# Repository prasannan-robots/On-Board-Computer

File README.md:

## Low Cost Onboard pcb for cubesat
Features:
- Redundant Control
- i2c external communication
- Power via 5v 3.3v
- Inbuilt temperature Monitoring

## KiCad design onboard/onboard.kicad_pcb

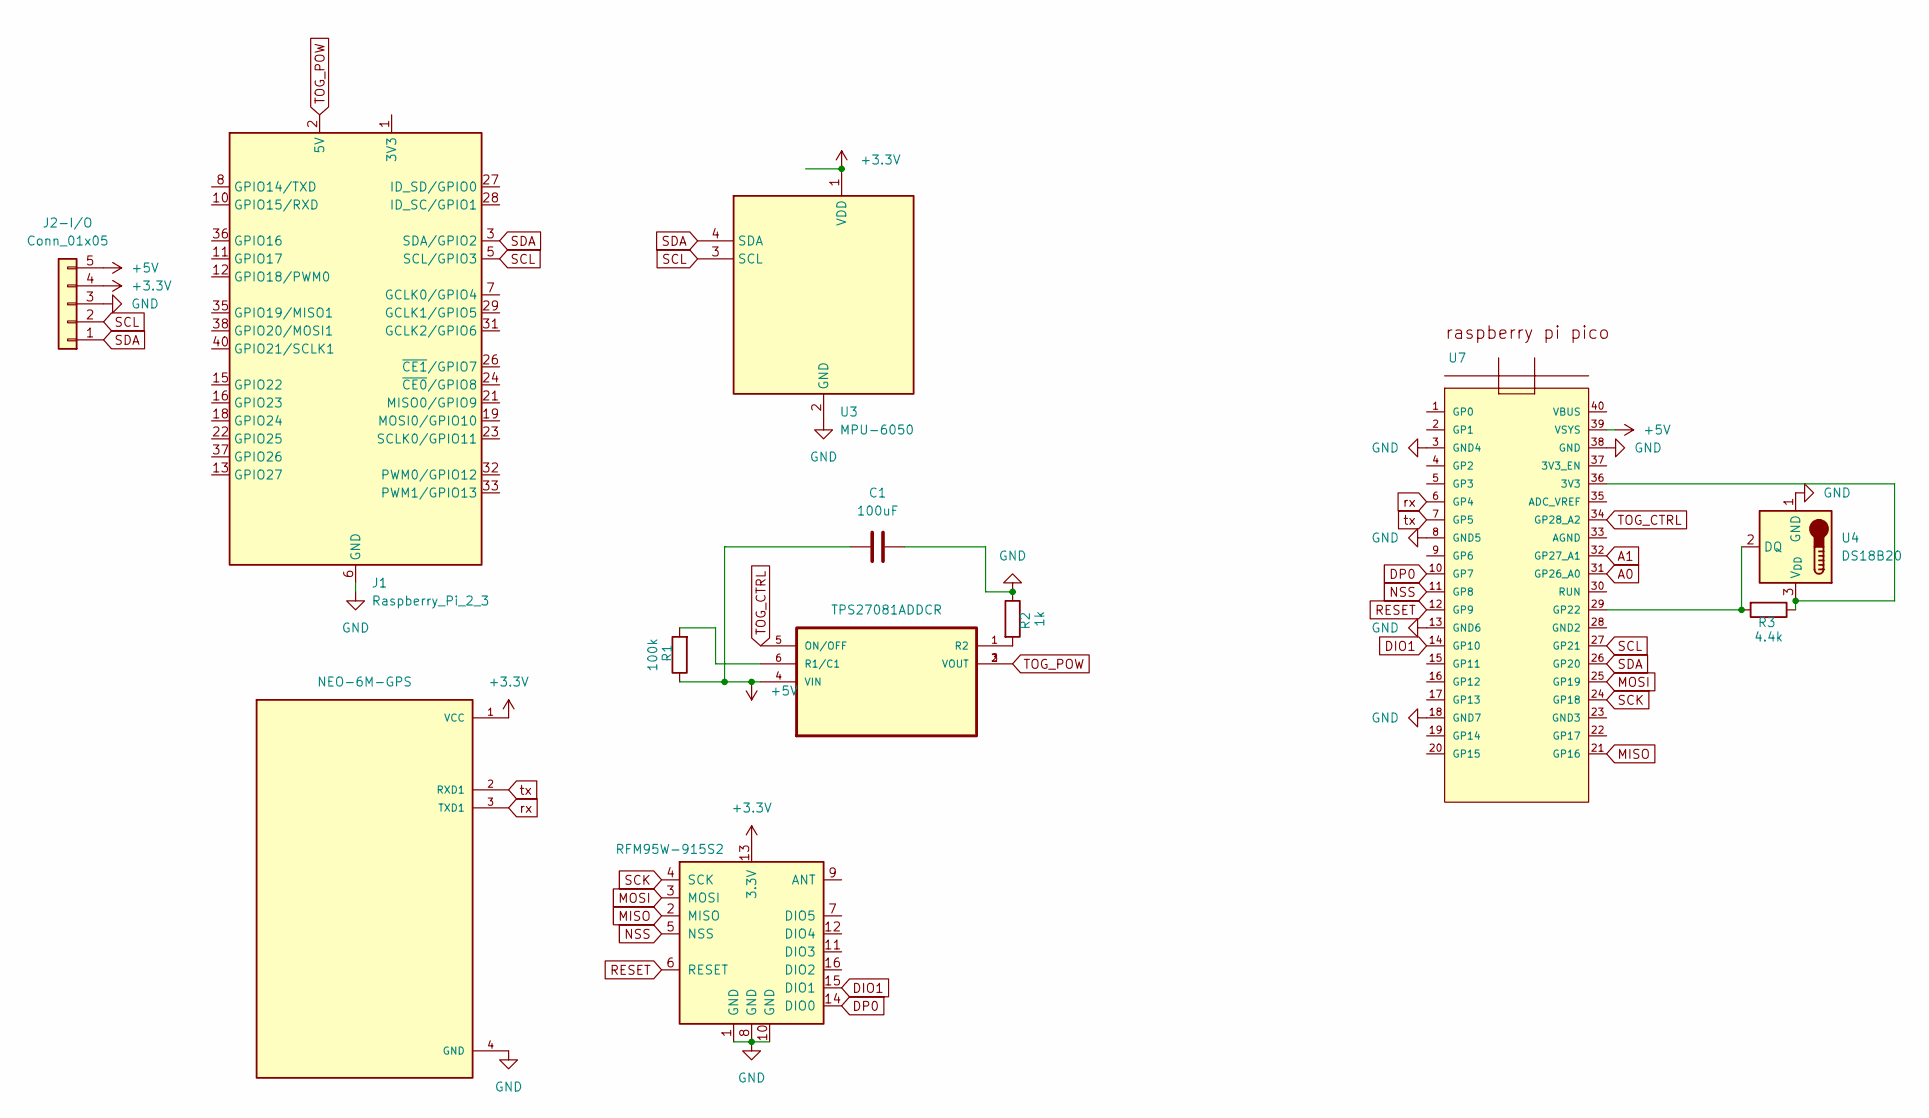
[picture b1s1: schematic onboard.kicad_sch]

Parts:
C1: 100uF; CP_Radial_D6.3mm_P2.50mm
J1: Raspberry_Pi_2_3; PinSocket_2x20_P2.54mm_Vertical
J2-I/O: Conn_01x05; PinSocket_1x05_P2.54mm_Vertical
R1: 100k; R_Axial_DIN0204_L3.6mm_D1.6mm_P7.62mm_Horizontal
R2: 1k; R_Axial_DIN0204_L3.6mm_D1.6mm_P7.62mm_Horizontal
R3: 4.4k; R_Axial_DIN0204_L3.6mm_D1.6mm_P7.62mm_Horizontal
U1: RFM95W-915S2; HOPERF_RFM9XW_THT
U2: NEO-6M-GPS; PinSocket_1x04_P2.54mm_Vertical; PARTREV R15
U3: MPU-6050; PinSocket_1x08_P2.54mm_Vertical
U4: DS18B20; TO-92_Inline
U5: TPS27081ADDCR; SOT95P280X110-6N
U7: RASPBERRY_PI_PICO; RaspberryPi_Pico_Common_THT

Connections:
+3.3V: J2-I/O.4, U1.13 (3.3V), U2.1 (VCC), U3.1 (VDD)
+5V: C1.1, J2-I/O.5, R1.1, U5.4 (VIN), U7.39 (VSYS)
A0: U7.31 (GP26_A0)
A1: U7.32 (GP27_A1)
DIO1: U1.15 (DIO1), U7.14 (GP10)
DP0: U1.14 (DIO0), U7.10 (GP7)
GND: C1.2, J1.6 (GND), J1.9 (GND), J1.14 (GND), J1.20 (GND), J1.25 (GND), J1.30 (GND), J1.34 (GND), J1.39 (GND), J2-I/O.3, R2.1, U1.1 (GND), U1.8 (GND), U1.10 (GND), U2.4 (GND), U3.2 (GND), U4.1 (GND), U7.3 (GND4), U7.8 (GND5), U7.13 (GND6), U7.18 (GND7), U7.38 (GND)
MISO: U1.2 (MISO), U7.21 (GP16)
MOSI: U1.3 (MOSI), U7.25 (GP19)
NSS: U1.5 (NSS), U7.11 (GP8)
unnamed: J1.1 (3V3), J1.17 (3V3)
unnamed: R3.2, U4.2 (DQ), U7.29 (GP22)
unnamed: R3.1, U4.3 (V_{DD}), U7.36 (3V3)
unnamed: R1.2, U5.6 (R1/C1)
unnamed: R2.2, U5.1 (R2)
RESET: U1.6 (RESET), U7.12 (GP9)
SCK: U1.4 (SCK), U7.24 (GP18)
SCL: J1.5 (SCL/GPIO3), J2-I/O.2, U3.3 (SCL), U7.27 (GP21)
SDA: J1.3 (SDA/GPIO2), J2-I/O.1, U3.4 (SDA), U7.26 (GP20)
TOG_CTRL: U5.5 (ON/OFF), U7.34 (GP28_A2)
TOG_POW: J1.2 (5V), J1.4 (5V), U5.2 (VOUT), U5.3 (VOUT)
rx: U2.3 (TXD1), U7.6 (GP4)
tx: U2.2 (RXD1), U7.7 (GP5)

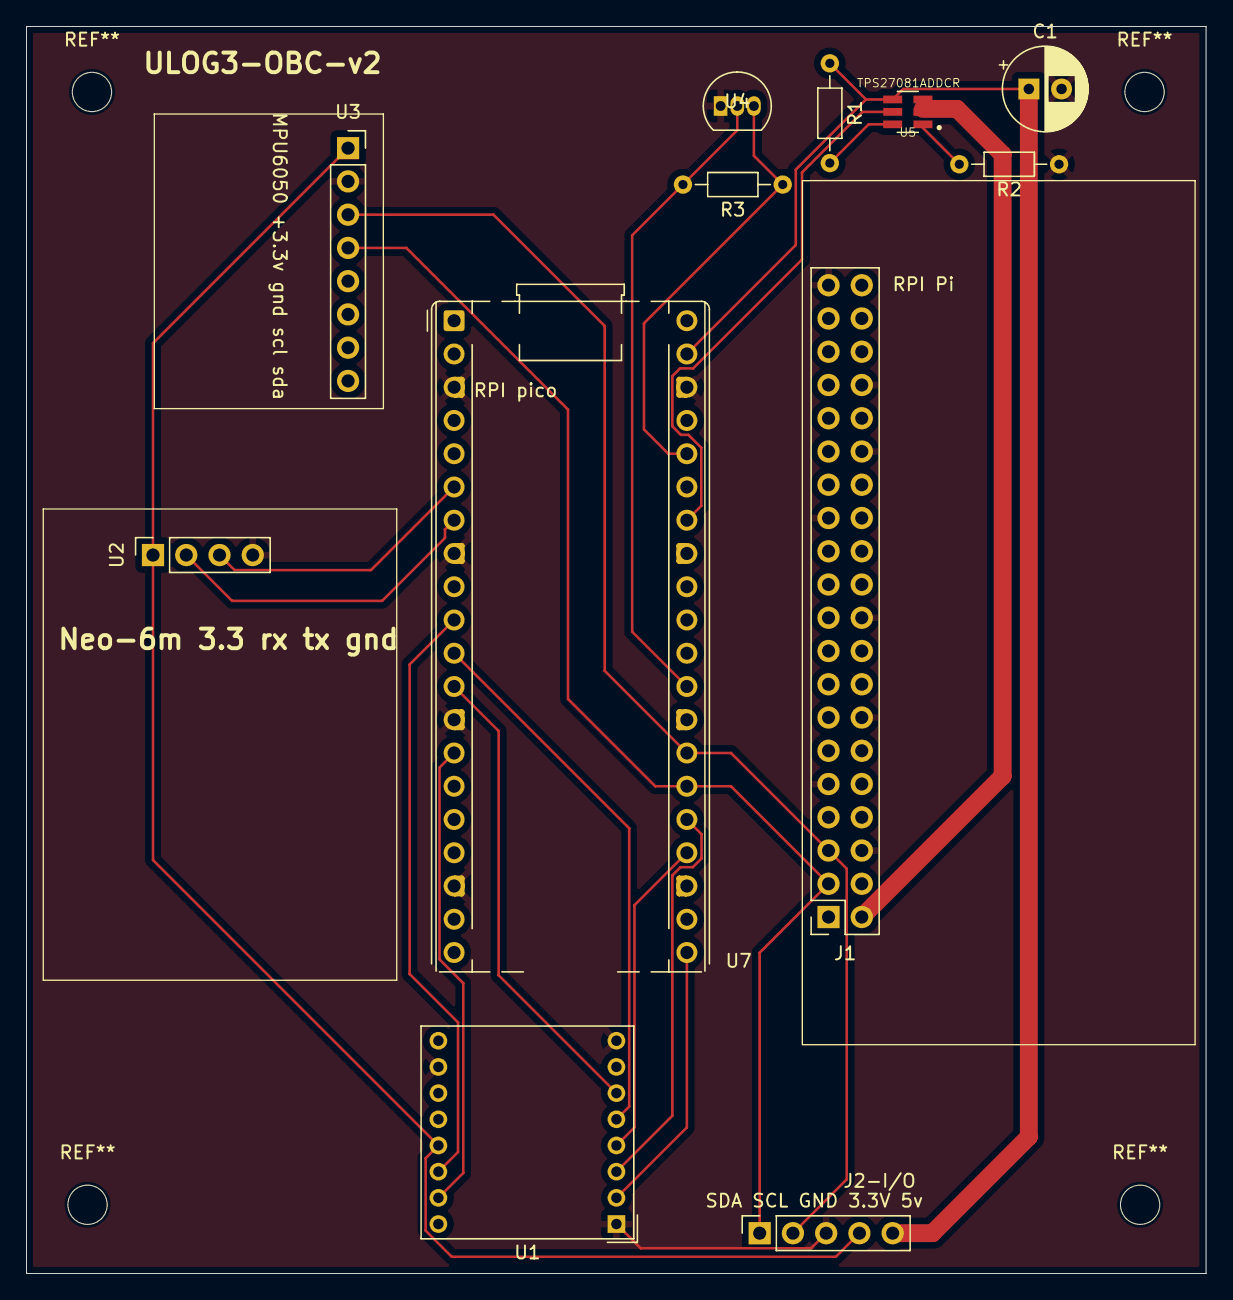
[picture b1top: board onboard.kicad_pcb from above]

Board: 2 copper layers, 90.1 x 95.2 mm, 12 parts (0 on the bottom side), 21 nets.

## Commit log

2025-02-14 [Feat] v2.0
2025-02-14 [Fix] Added README
